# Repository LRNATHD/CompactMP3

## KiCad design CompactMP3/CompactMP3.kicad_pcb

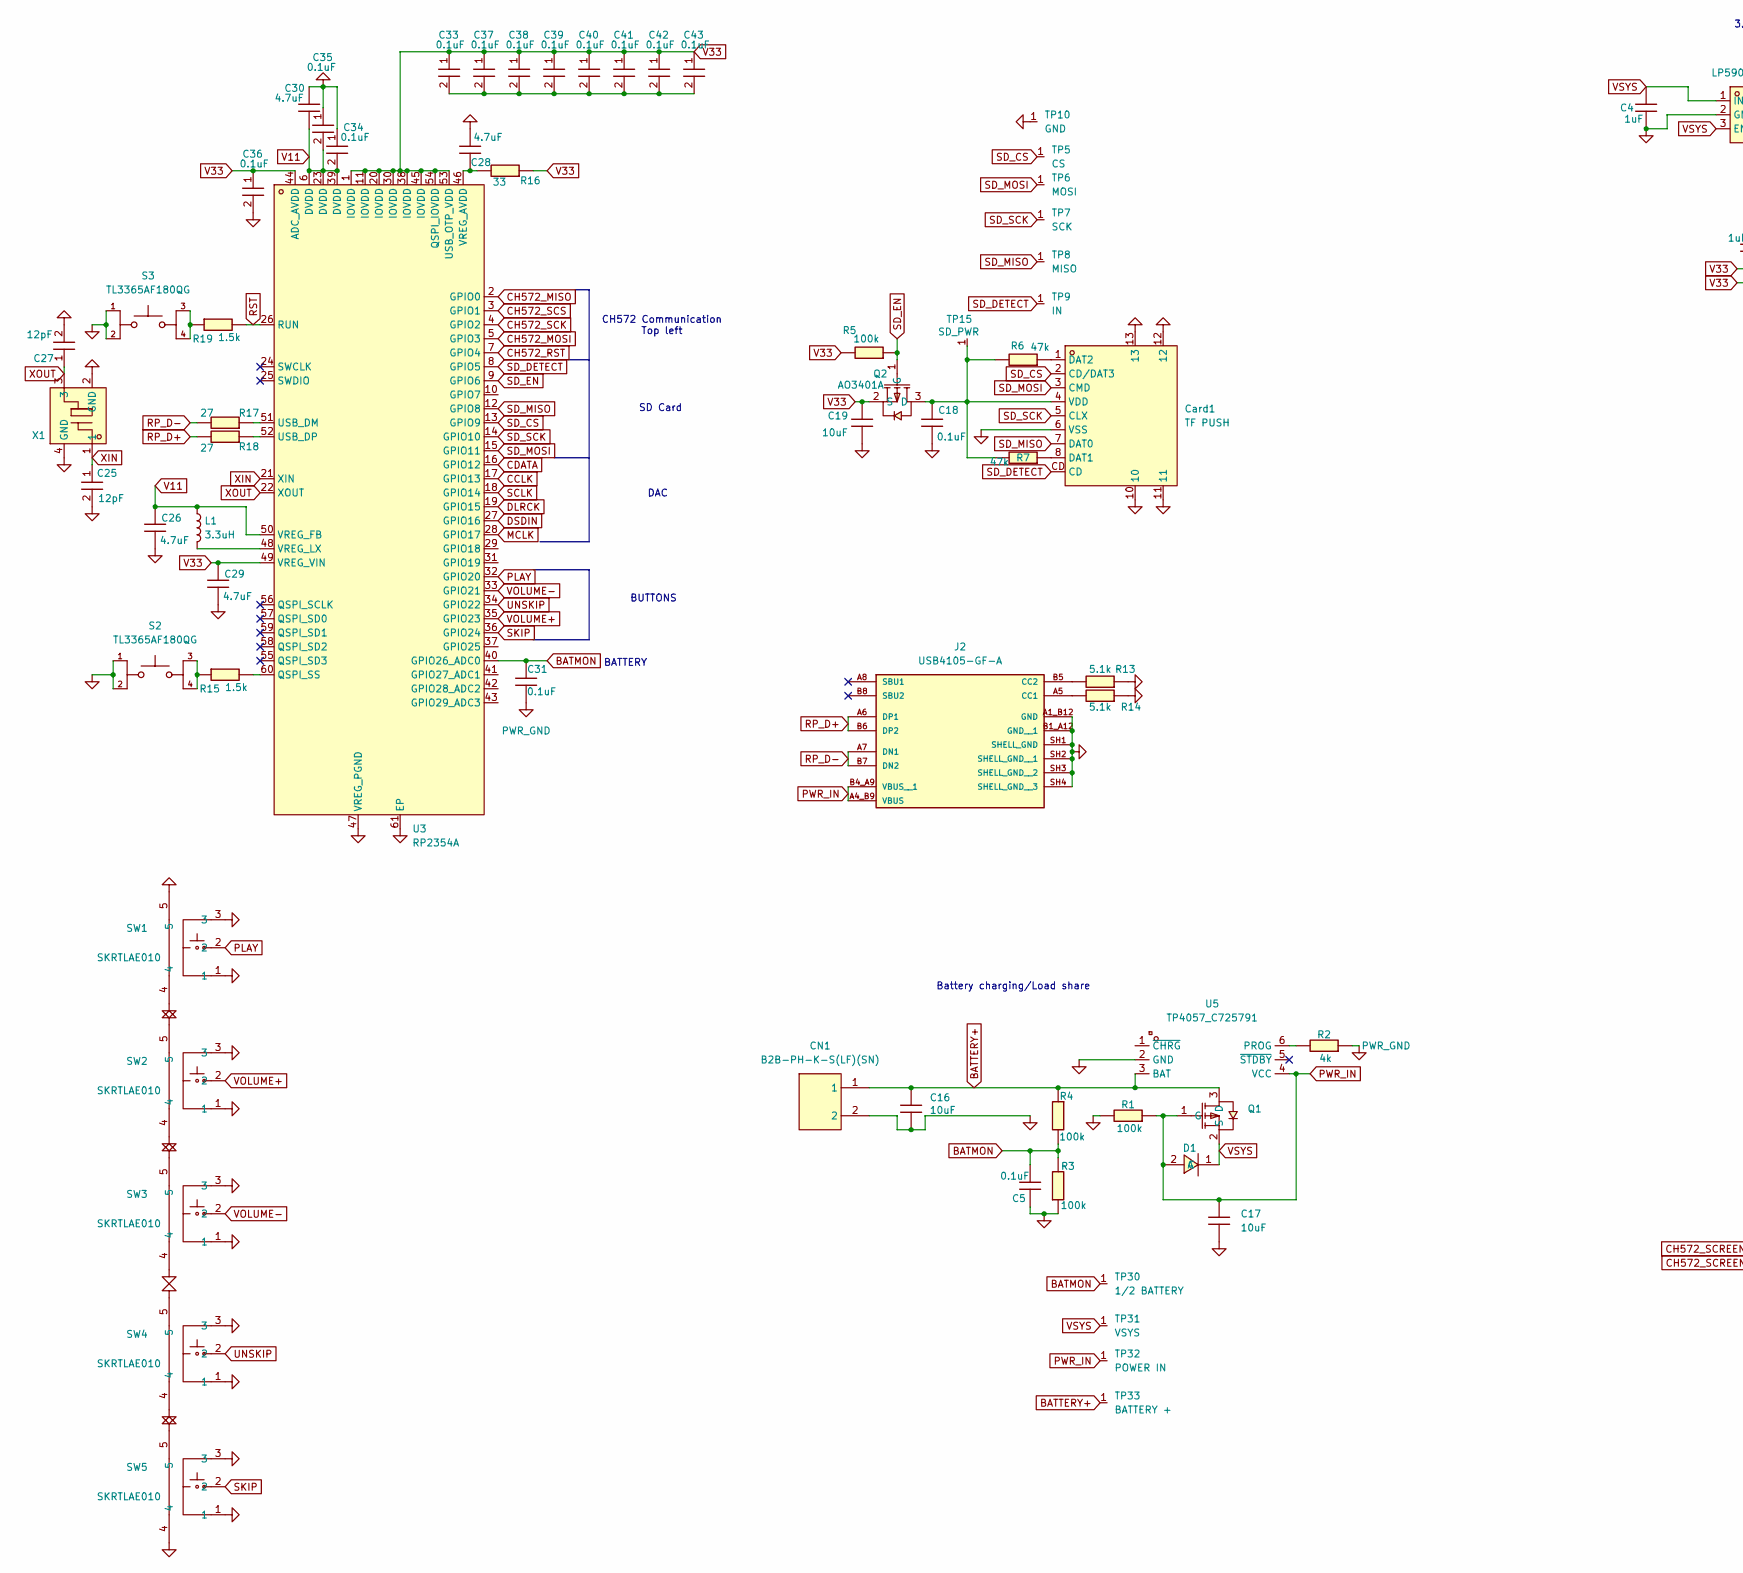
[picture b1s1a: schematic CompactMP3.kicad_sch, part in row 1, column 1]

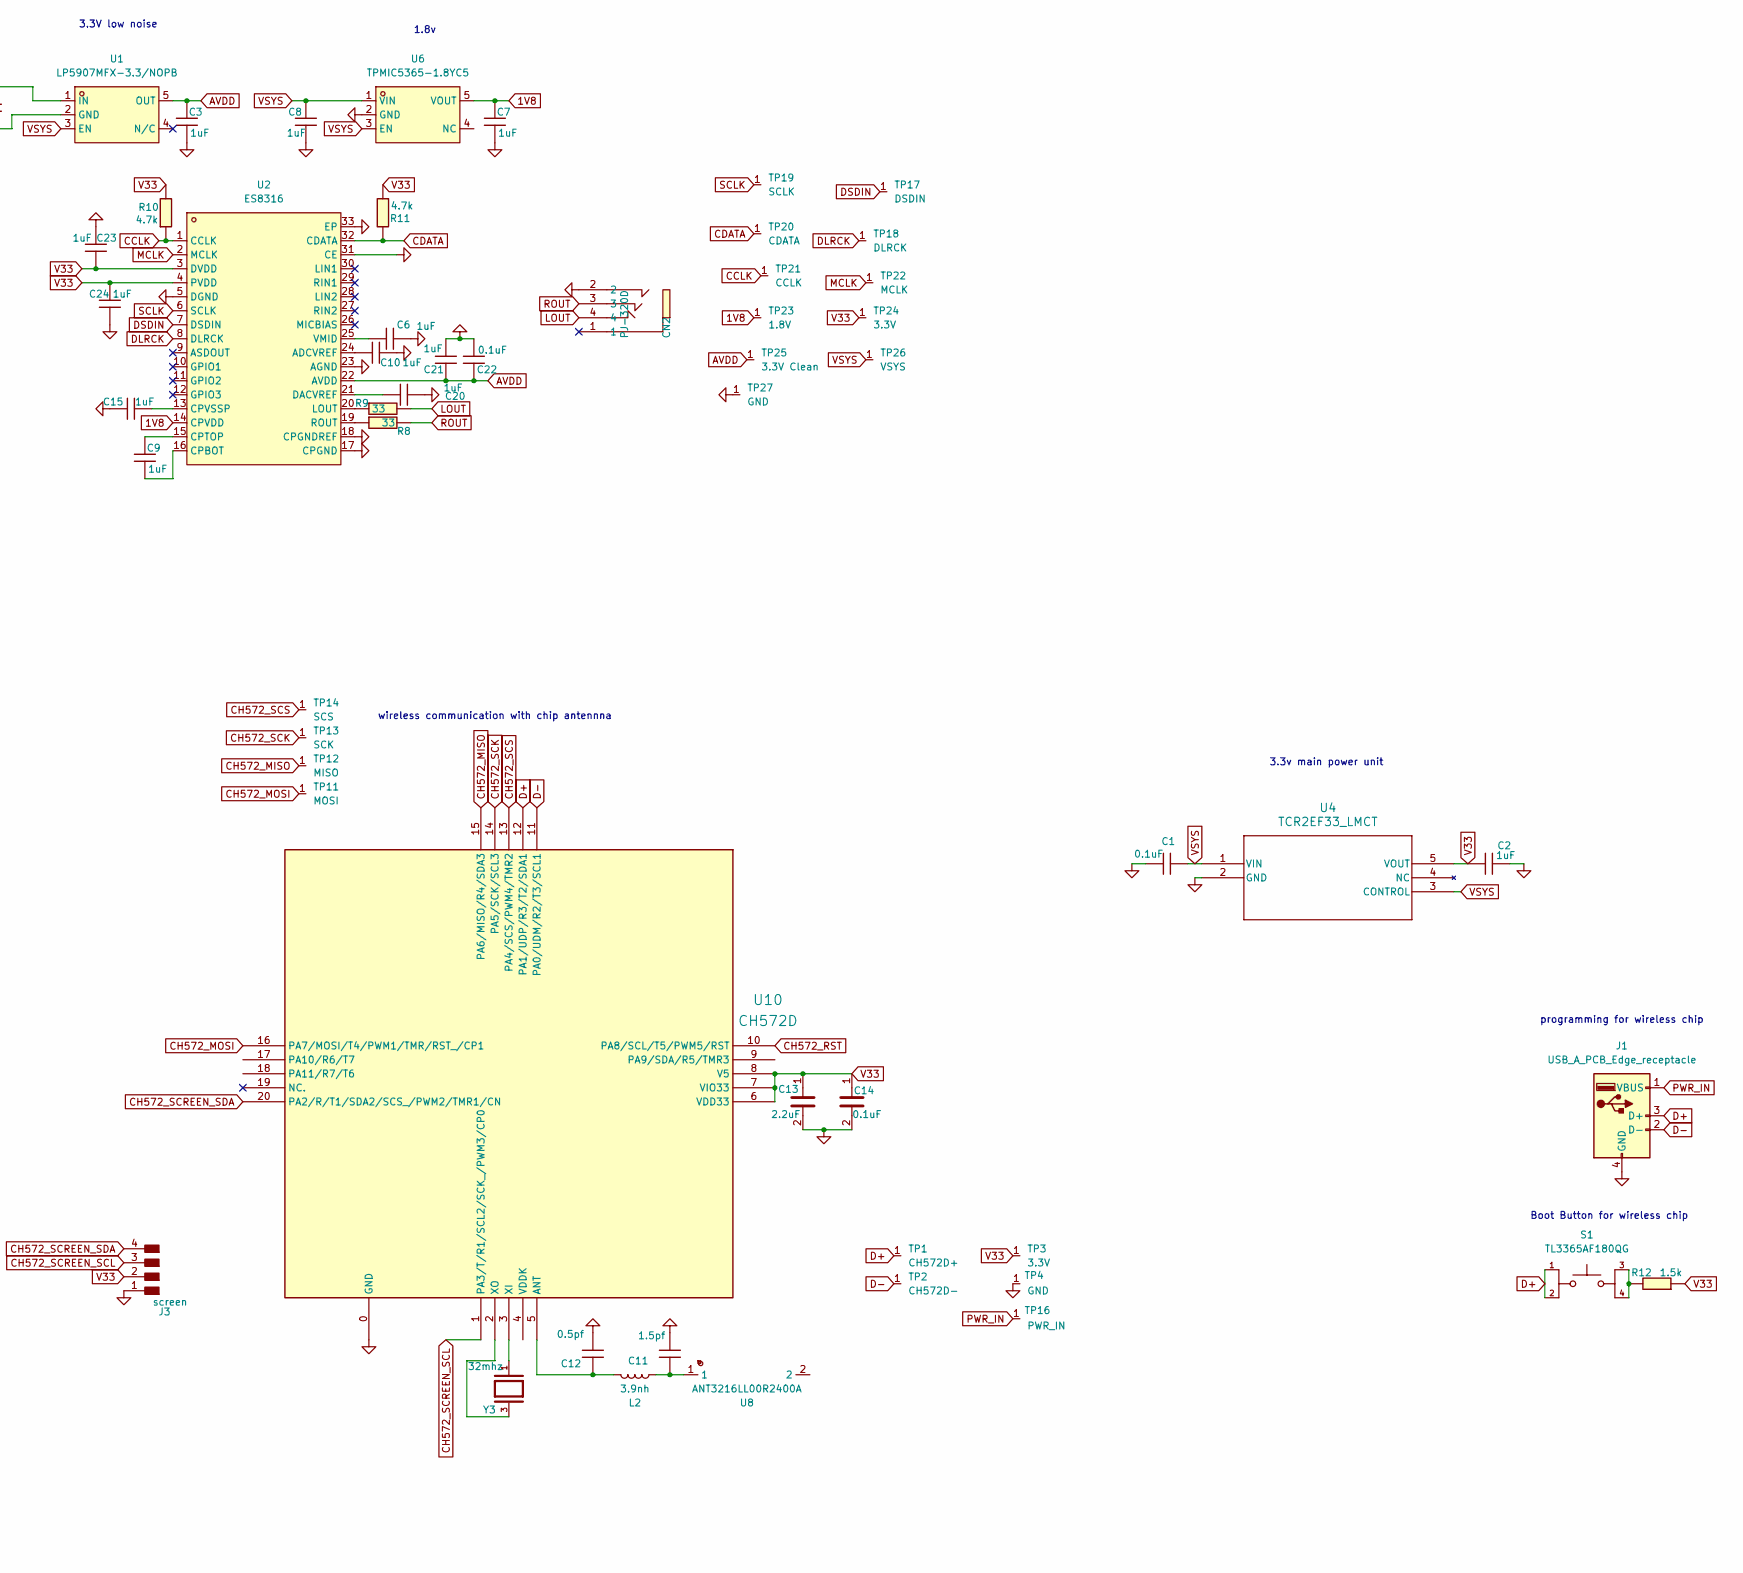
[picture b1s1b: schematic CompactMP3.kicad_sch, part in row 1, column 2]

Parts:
C1, C5, C14, C18, C22, C31, C33, C34, C35, C36, C37, C38, C39, C40, C41, C42, C43: 0.1uF; 0402
C2, C3, C4, C6, C7, C8, C9, C10, C15, C20, C21, C23, C24: 1uF; 0402
C11: 1.5pf; 0603
C12: 0.5pf; 0603
C13: 2.2uF; 0603
C16, C17, C19: 10uF; 0603
C25, C27: 12pF; 0402
C26, C28, C29, C30: 4.7uF; 0603
CN1: B2B-PH-K-S(LF)(SN); CONN-TH_B2B-PH-K-S; LCSC Part C131337
CN2: PJ-320D; AUDIO-SMD_PJ-320D-1; LCSC Part C431535
Card1: TF PUSH; TF-SMD_TF-PUSH; LCSC Part C393941
D1: SS14_C2837270; SOD-123FL_L2.8-W1.8-LS3.7-RD; LCSC Part C2837270
J1: USB_A_PCB_Edge_receptacle
J2: USB4105-GF-A; usbc; PARTREV B4
J3: screen; PinHeader_01x04_P2.54mm_Vertical_THT_D1mm
L1: 3.3uH; 0603
L2: 3.9nh; 0603
Q1, Q2: AO3401A; SOT-23_L2.9-W1.3-P1.90-LS2.4-BR; LCSC Part C15127
R1, R3, R4, R5: 100k; 0603
R2: 4k; 0603
R6, R7: 47k; 0603
R8, R9, R16: 33; 0603
R10, R11: 4.7k; 0603
R12, R15, R19: 1.5k; 0603
R13, R14: 5.1k; 0603
R17, R18: 27; 0603
S1, S2, S3: TL3365AF180QG; button; PARTREV A
SW1, SW2, SW3, SW4, SW5: SKRTLAE010; KEY-SMD_SKRTLAE010; LCSC Part C110293
TP1: CH572D+; SMD_TP_0.8mm
TP2: CH572D-; SMD_TP_0.8mm
TP3, TP24: 3.3V; SMD_TP_0.8mm
TP4, TP10, TP27: GND; SMD_TP_0.8mm
TP5: CS; SMD_TP_0.8mm
TP6, TP11: MOSI; SMD_TP_0.8mm
TP7, TP13: SCK; SMD_TP_0.8mm
TP8, TP12: MISO; SMD_TP_0.8mm
TP9: IN; SMD_TP_0.8mm
TP14: SCS; SMD_TP_0.8mm
TP15: SD_PWR; SMD_TP_0.8mm
TP16: PWR_IN; SMD_TP_0.8mm
TP17: DSDIN; SMD_TP_0.8mm
TP18: DLRCK; SMD_TP_0.8mm
TP19: SCLK; SMD_TP_0.8mm
TP20: CDATA; SMD_TP_0.8mm
TP21: CCLK; SMD_TP_0.8mm
TP22: MCLK; SMD_TP_0.8mm
TP23: 1.8V; SMD_TP_0.8mm
TP25: 3.3V Clean; SMD_TP_0.8mm
TP26, TP31: VSYS; SMD_TP_0.8mm
TP30: 1/2 BATTERY; SMD_TP_0.8mm
TP32: POWER IN; SMD_TP_0.8mm
TP33: BATTERY +; SMD_TP_0.8mm
U1: LP5907MFX-3.3/NOPB; SOT-23-5_L3.0-W1.7-P0.95-LS2.8-BR; LCSC Part C80670
U2: ES8316; QFN-32_L4.0-W4.0-P0.40-BL-EP2.7; LCSC Part C365735
U3: RP2354A; QFN-60_L7.0-W7.0-P0.40-TL-EP3.4; LCSC Part C41378174
U4: TCR2EF33_LMCT; voltage regulator
U5: TP4057_C725791; SOT-23-6_L2.9-W1.6-P0.95-LS2.8-BR; LCSC Part C725791
U6: TPMIC5365-1.8YC5; SOT-323-5_L2.1-W1.3-P0.65-LS2.1-BL; LCSC Part C3021118
U8: ANT3216LL00R2400A; ANT-SMD_L3.2-W1.6; LCSC Part C293767
U10: CH572D; QFN20_3X3
X1: XTM32012000JT00351006; CRYSTAL-SMD_4P-L3.2-W2.5-BL; LCSC Part C37635370
Y3: 32mhz; 32mhz crystal; PARTREV N/A

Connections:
1V8: C7.1, TP23.1, U2.14 (CPVDD), U6.5 (VOUT)
AVDD: C3.1, C21.1, C22.1, TP25.1, U1.5 (OUT), U2.22 (AVDD)
BATMON: C5.2, C31.1, R3.1, R4.1, TP30.1, U3.40 (GPIO26_ADC0)
BATTERY+: C16.1, CN1.1, Q1.3 (D), R4.2, TP33.1, U5.3 (BAT)
CCLK: R10.2, TP21.1, U2.1 (CCLK), U3.17 (GPIO13)
CDATA: R11.1, TP20.1, U2.32 (CDATA), U3.16 (GPIO12)
CH572_MISO: TP12.1, U3.2 (GPIO0), U10.15 (PA6/MISO/R4/SDA3)
CH572_MOSI: TP11.1, U3.5 (GPIO3), U10.16 (PA7/MOSI/T4/PWM1/TMR/RST_/CP1)
CH572_RST: U3.7 (GPIO4), U10.10 (PA8/SCL/T5/PWM5/RST)
CH572_SCK: TP13.1, U3.4 (GPIO2), U10.14 (PA5/SCK/SCL3)
CH572_SCREEN_SCL: J3.3, U10.1 (PA3/T/R1/SCL2/SCK_/PWM3/CP0)
CH572_SCREEN_SDA: J3.4, U10.20 (PA2/R/T1/SDA2/SCS_/PWM2/TMR1/CN)
CH572_SCS: TP14.1, U3.3 (GPIO1), U10.13 (PA4/SCS/PWM4/TMR2)
D+: J1.3 (D+), S1.1, S1.2, TP1.1, U10.12 (PA1/UDP/R3/T2/SDA1)
D-: J1.2 (D-), TP2.1, U10.11 (PA0/UDM/R2/T3/SCL1)
DLRCK: TP18.1, U2.8 (DLRCK), U3.19 (GPIO15)
DSDIN: TP17.1, U2.7 (DSDIN), U3.27 (GPIO16)
LOUT: CN2.4, R8.1
MCLK: TP22.1, U2.2 (MCLK), U3.28 (GPIO17)
unnamed: C11.1, L2.1, U8.1 (1_1)
unnamed: C33.2, C37.2, C38.2, C39.2, C40.2, C41.2, C42.2, C43.2
unnamed: Card1.8 (DAT1), R7.2
unnamed: Card1.1 (DAT2), R6.2
unnamed: J2.A5 (CC1), R14.1
unnamed: J2.B5 (CC2), R13.1
unnamed: R12.1, S1.3, S1.4
unnamed: R15.2, S2.3, S2.4
unnamed: R19.2, S3.3, S3.4
unnamed: C10.1, U2.24 (ADCVREF)
unnamed: C9.2, U2.16 (CPBOT)
unnamed: C9.1, U2.15 (CPTOP)
unnamed: C15.2, U2.13 (CPVSSP)
unnamed: C20.2, U2.21 (DACVREF)
unnamed: R8.2, U2.20 (LOUT)
unnamed: R9.2, U2.19 (ROUT)
unnamed: C6.1, U2.25 (VMID)
unnamed: R15.1, U3.60 (QSPI_SS)
unnamed: R17.2, U3.51 (USB_DM)
unnamed: R18.2, U3.52 (USB_DP)
unnamed: C28.2, R16.1, U3.46 (VREG_AVDD)
unnamed: L1.2, U3.48 (VREG_LX)
unnamed: R2.1, U5.6 (PROG)
unnamed: C12.1, L2.2, U10.5 (ANT)
unnamed: U10.3 (XI), Y3.1
unnamed: U10.2 (XO), Y3.3
PLAY: SW1.2, U3.32 (GPIO20)
PWR_GND: C1.1, C2.2, C3.2, C4.1, C5.1, C6.2, C7.2, C8.2, C10.2, C11.2, C12.2, C13.2, C14.2, C15.1, C16.2, C17.2, C18.2, C19.2, C20.1, C21.2, C22.2, C23.1, C24.1, C25.2, C26.2, C27.2, C28.1, C29.2, C30.1, C31.2, C34.1, C35.1, C36.2, CN1.2, CN2.2, Card1.6 (VSS), Card1.10, Card1.11, Card1.12, Card1.13, J1.4 (GND), J2.A1_B12 (GND), J2.B1_A12 (GND__1), J2.SH1 (SHELL_GND), J2.SH2 (SHELL_GND__1), J2.SH3 (SHELL_GND__2), J2.SH4 (SHELL_GND__3), J3.1, R1.1, R2.2, R3.2, R13.2, R14.2, S2.1, S2.2, S3.1, S3.2, SW1.1, SW1.3, SW1.4, SW1.5, SW2.1, SW2.3, SW2.4, SW2.5, SW3.1, SW3.3, SW3.4, SW3.5, SW4.1, SW4.3, SW4.4, SW4.5, SW5.1, SW5.3, SW5.4, SW5.5, TP4.1, TP10.1, TP27.1, U1.2 (GND), U2.5 (DGND), U2.17 (CPGND), U2.18 (CPGNDREF), U2.23 (AGND), U2.31 (CE), U2.33 (EP), U3.47 (VREG_PGND), U3.61 (EP), U4.2 (GND), U5.2 (GND), U6.2 (GND), U10.0 (GND), X1.2 (GND), X1.4 (GND)
PWR_IN: C17.1, D1.2 (A), J1.1 (VBUS), J2.A4_B9 (VBUS), J2.B4_A9 (VBUS__1), Q1.1 (G), R1.2, TP16.1, TP32.1, U5.4 (VCC)
ROUT: CN2.3, R9.1
RP_D+: J2.A6 (DP1), J2.B6 (DP2), R18.1
RP_D-: J2.A7 (DN1), J2.B7 (DN2), R17.1
RST: R19.1, U3.26 (RUN)
SCLK: TP19.1, U2.6 (SCLK), U3.18 (GPIO14)
SD_CS: Card1.2 (CD/DAT3), TP5.1, U3.13 (GPIO9)
SD_DETECT: Card1.CD, TP9.1, U3.8 (GPIO5)
SD_EN: Q2.1 (G), R5.2, U3.9 (GPIO6)
SD_MISO: Card1.7 (DAT0), TP8.1, U3.12 (GPIO8)
SD_MOSI: Card1.3 (CMD), TP6.1, U3.15 (GPIO11)
SD_SCK: Card1.5 (CLX), TP7.1, U3.14 (GPIO10)
SKIP: SW5.2, U3.36 (GPIO24)
UNSKIP: SW4.2, U3.34 (GPIO22)
V11: C26.1, C30.2, C34.2, C35.2, L1.1, U3.6 (DVDD), U3.23 (DVDD), U3.39 (DVDD), U3.50 (VREG_FB)
V33: C2.1, C13.1, C14.1, C19.1, C23.2, C24.2, C29.1, C33.1, C36.1, C37.1, C38.1, C39.1, C40.1, C41.1, C42.1, C43.1, J3.2, Q2.2 (S), R5.1, R10.1, R11.2, R12.2, R16.2, TP3.1, TP24.1, U2.3 (DVDD), U2.4 (PVDD), U3.1 (IOVDD), U3.11 (IOVDD), U3.20 (IOVDD), U3.30 (IOVDD), U3.38 (IOVDD), U3.44 (ADC_AVDD), U3.45 (IOVDD), U3.49 (VREG_VIN), U3.53 (USB_OTP_VDD), U3.54 (QSPI_IOVDD), U4.5 (VOUT), U10.6 (VDD33), U10.7 (VIO33), U10.8 (V5)
VOLUME+: SW2.2, U3.35 (GPIO23)
VOLUME-: SW3.2, U3.33 (GPIO21)
VSYS: C1.2, C4.2, C8.1, D1.1 (C), Q1.2 (S), TP26.1, TP31.1, U1.1 (IN), U1.3 (EN), U4.1 (VIN), U4.3 (CONTROL), U6.1 (VIN), U6.3 (EN)
XIN: C25.1, U3.21 (XIN), X1.1
XOUT: C27.1, U3.22 (XOUT), X1.3

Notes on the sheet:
DAC
SD Card
programming for wireless chip
1.8v
Battery charging/Load share
Boot Button for wireless chip
CH572 Communication Top left
BUTTONS
wireless communication with chip antennna
3.3V low noise
BATTERY
3.3v main power unit

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
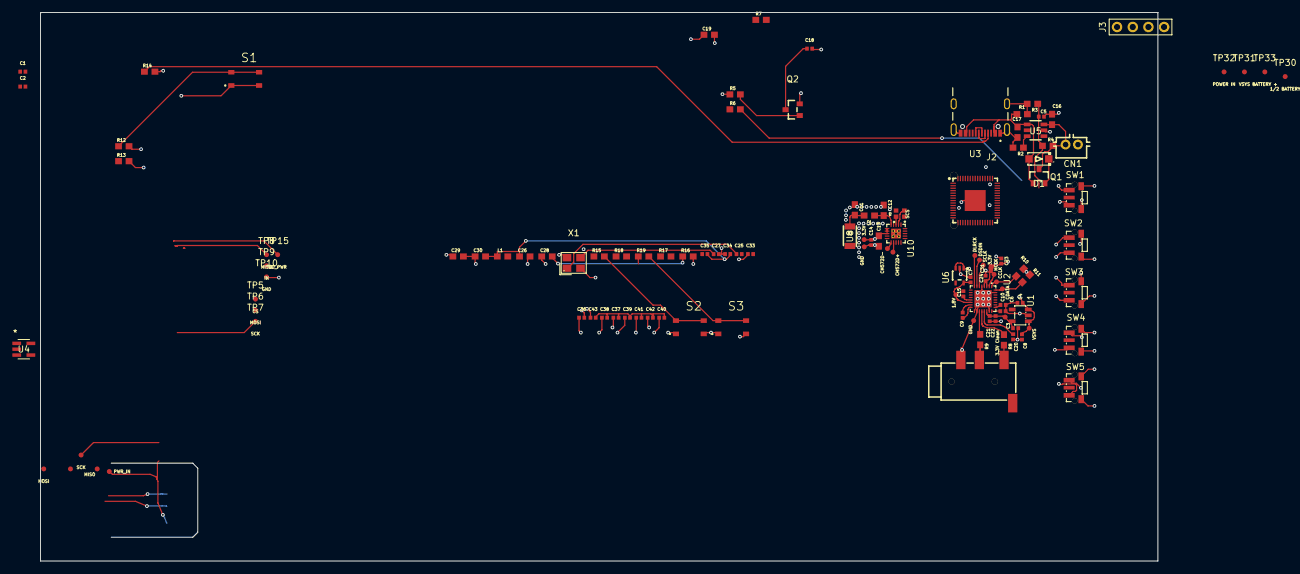
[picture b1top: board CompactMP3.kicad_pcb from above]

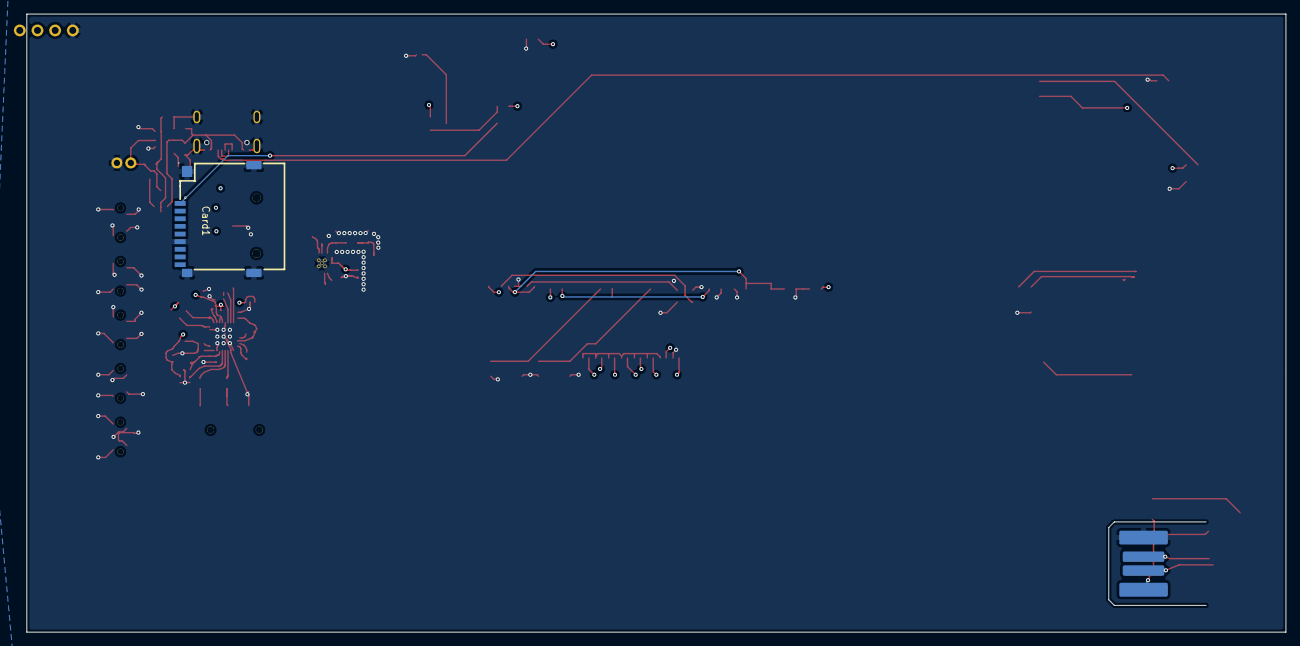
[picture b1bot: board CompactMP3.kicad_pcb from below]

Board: 4 copper layers, 181.1 x 88.9 mm, 121 parts (2 on the bottom side), 70 nets.

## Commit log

2026-02-26 started work, sleepy
2026-03-02 alot of work worked on, layout started
2026-03-03 more work, ch572d section start (not done
2026-03-04 more work, barely any
2026-03-15 a buncha changes, nearing done but still time to work
2026-06-01 worked on it
